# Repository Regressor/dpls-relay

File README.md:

# Реле для С2000-КДЛ (на базе таблички С2000-ОСТ)

Мне понадобилось на базе уже имеющейся адресной охрано-пожарной системы с ДПЛС шиной реализовать включение-выключение нагрузки 220В по команде пульта. При этом реле необходимо было установить в стандартный подрозетник.

Размеры С2000-СП к сожалению не подходили, поэтому было принято решение купить табличку С2000-ОСТ, снять с нее микроконтроллер, разработать плату для этого микроконтроллера размерами 21х54мм со всей 
необходимой обвязкой для работы шины ДПЛС и управления нагрузкой. Исходники платы в формате Kicad выкладываю в общий доступ.

Управление нагрузкой осуществляется с помощью симмистора BTA06-600. Опторазвязка сделана на базе IL4208 (потребление устройства ограничено шиной ДПЛС поэтому выбрана самая малопотребляющая опторазвязка).

Под симмистор я рекомендую на плату наклеить несколько слоев каптона во избежание замыкания (см. фото).

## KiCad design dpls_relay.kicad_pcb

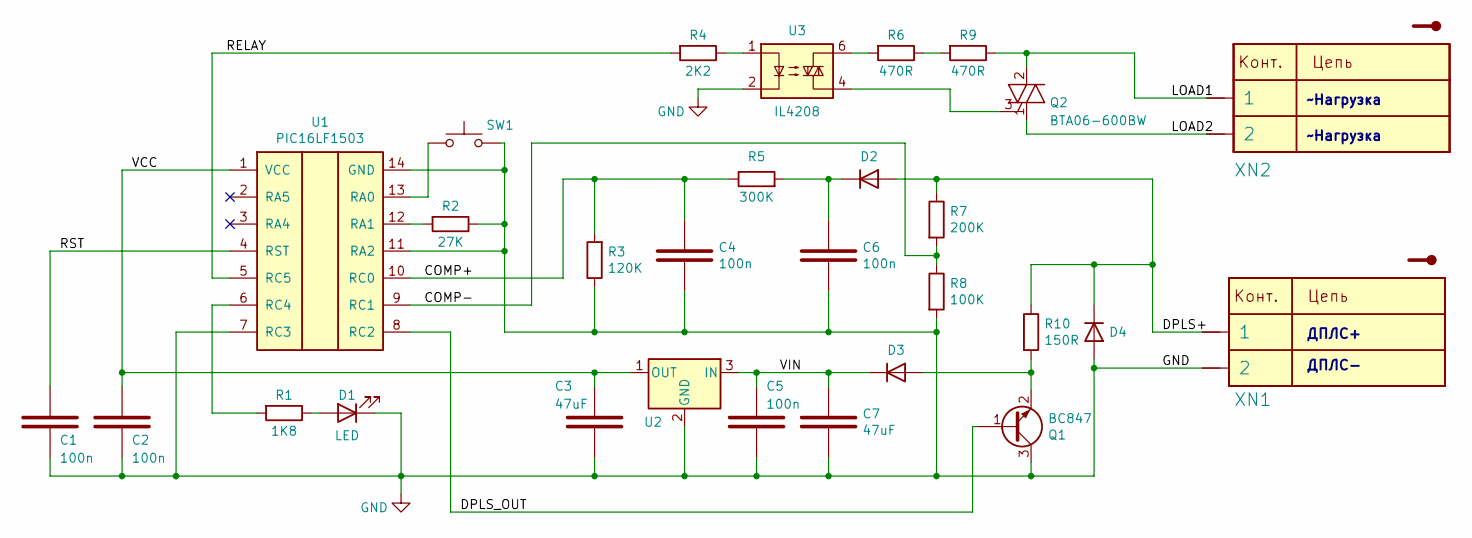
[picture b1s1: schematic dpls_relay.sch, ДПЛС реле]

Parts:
C1, C2, C4, C5, C6: 100n; C_0805_2012Metric
C3, C7: 47uF; C_1812_4532Metric
D1: LED; LED_0805_2012Metric
D2, D3, D4: PMEG4010BEA; D_SOD-323
Q1: BC847; SOT-23
Q2: BTA06-600BW; TO-220-3_Vertical
R1: 1K8; R_0805_2012Metric
R2: 27K; R_0805_2012Metric
R3: 120K; R_0805_2012Metric
R4: 2K2; R_0805_2012Metric
R5: 300K; R_0805_2012Metric
R6, R9: 470R; R_1206_3216Metric
R7: 200K; R_0805_2012Metric
R8: 100K; R_0805_2012Metric
R10: 150R; R_0805_2012Metric
SW1: SW_Push; SW_SPST_FSMSM
U1: PIC16LF1503; SO-14_3.9x8.65mm_P1.27mm
U2: L78L05; SOT-89-3
U3: IL4208; DIP-6_W7.62mm
XN1, XN2: HEAD_2PIN; KLS2-102

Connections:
/COMP+: C4.1, R3.2, R5.1, U1.10 (RC0)
/COMP-: R7.2, R8.1, U1.9 (RC1)
/DPLS+: D2.2 (A), D4.1 (K), R7.1, R10.1, XN1.1
/DPLS_OUT: Q1.1 (B), U1.8 (RC2)
/LOAD1: Q2.2, R9.1, XN2.1
/LOAD2: Q2.1, XN2.2
/RELAY: R4.2, U1.5 (RC5)
/RST: C1.1, U1.4 (RST)
/VCC: C2.2, C3.1, U1.1 (VCC), U2.1 (OUT)
/VIN: C5.1, C7.1, D3.1 (K), U2.3 (IN)
GND: C1.2, C2.1, C3.2, C4.2, C5.2, C6.2, C7.2, D1.1 (K), D4.2 (A), Q1.3 (C), R2.1, R3.1, R8.2, SW1.2, U1.7 (RC3), U1.11 (RA2), U1.14 (GND), U2.2 (GND), U3.2, XN1.2
unnamed: C6.1, D2.1 (K), R5.2
unnamed: D1.2 (A), R1.1
unnamed: D3.2 (A), Q1.2 (E), R10.2
unnamed: Q2.3, U3.4
unnamed: R1.2, U1.6 (RC4)
unnamed: R2.2, U1.12 (RA1)
unnamed: R4.1, U3.1
unnamed: R6.1, R9.2
unnamed: R6.2, U3.6
unnamed: SW1.1, U1.13 (RA0)

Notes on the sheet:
ДПЛС+
ДПЛС-
~~Нагрузка

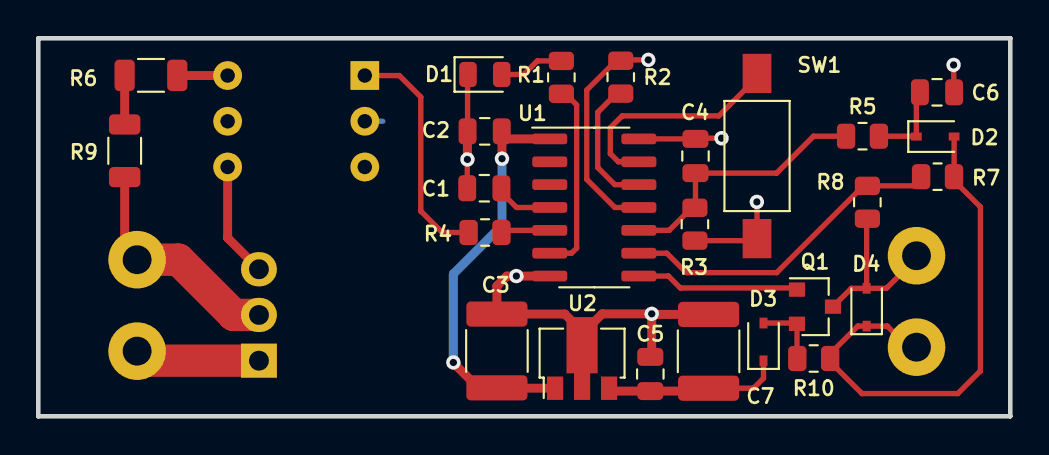
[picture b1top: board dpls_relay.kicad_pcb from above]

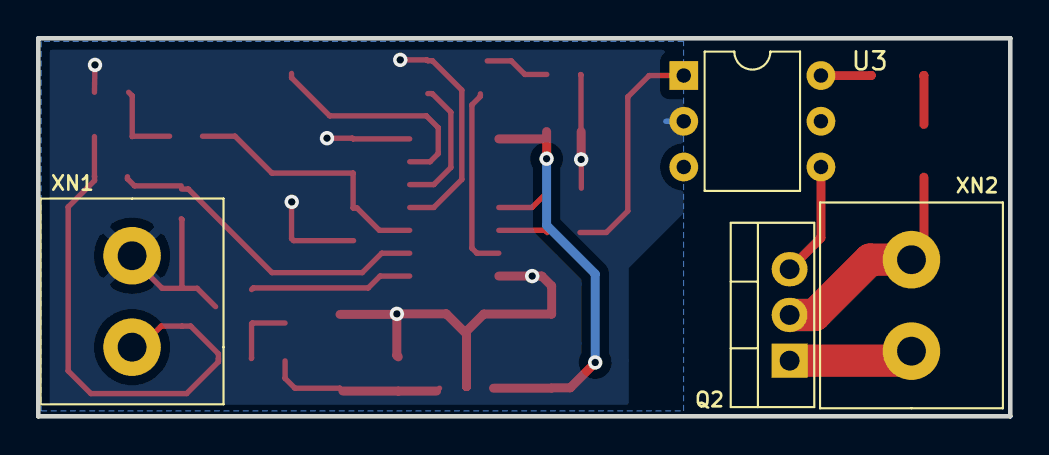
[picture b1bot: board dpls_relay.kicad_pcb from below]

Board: 2 copper layers, 54.0 x 21.0 mm, 29 parts (4 on the bottom side), 21 nets.

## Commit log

2023-03-01 Добавлены исходники платы и схемы, а также фотография
2023-03-01 Добавлена схема в формате pdf
2023-04-02 Update README.md
    Поправлен заголовок
